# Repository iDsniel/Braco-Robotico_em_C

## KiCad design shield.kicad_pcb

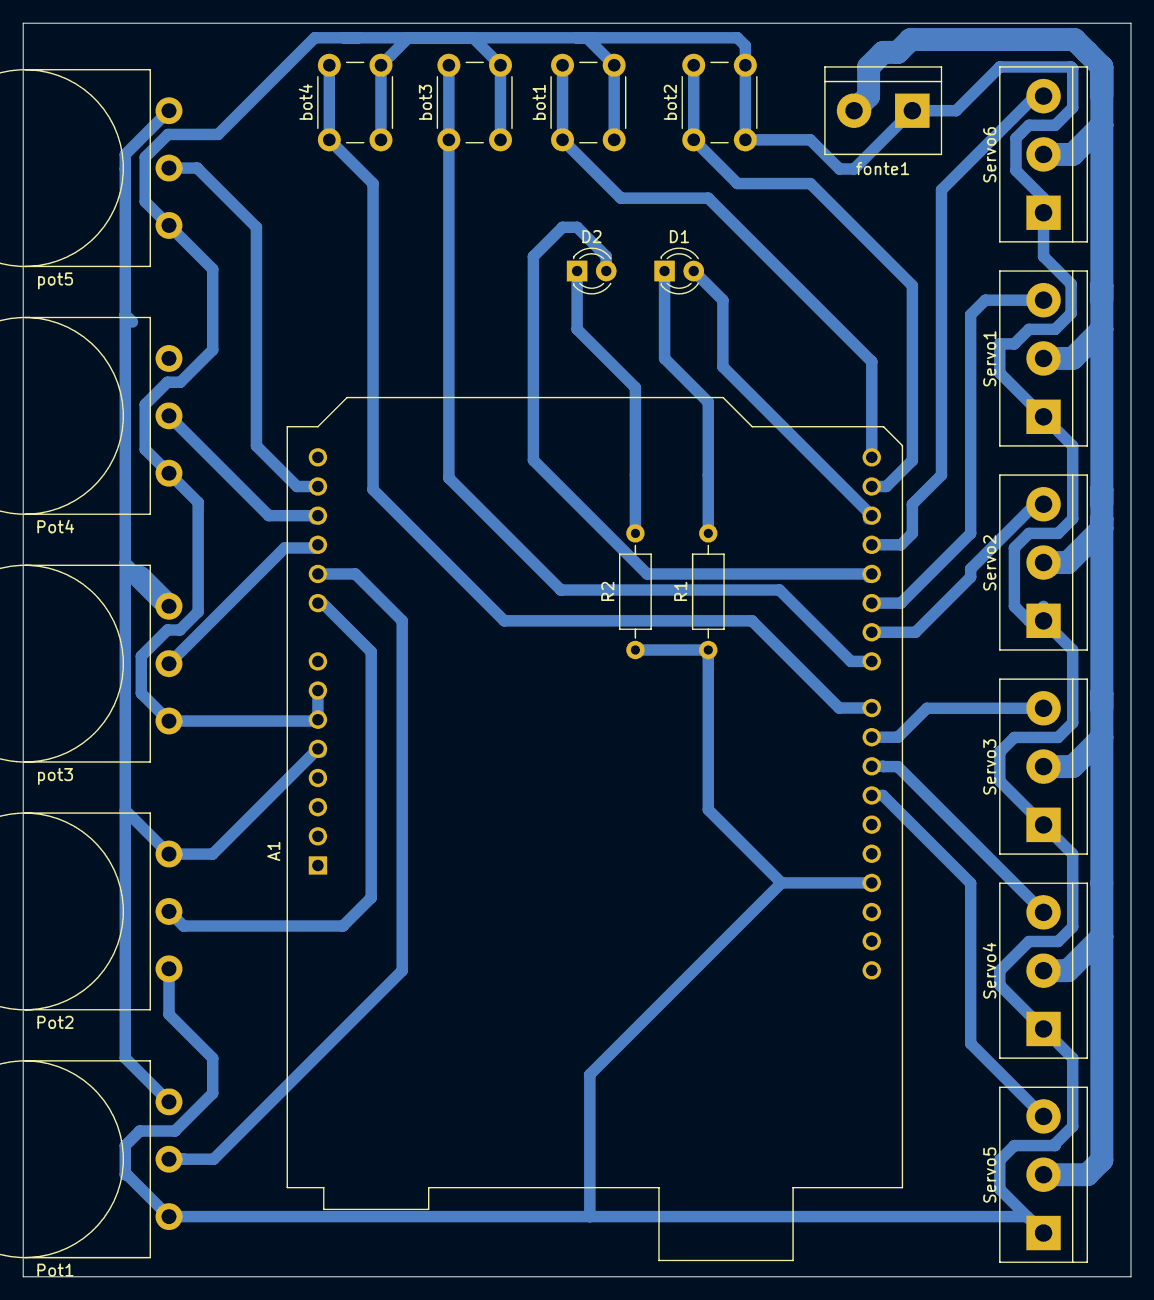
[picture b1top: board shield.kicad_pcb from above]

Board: 2 copper layers, 96.5 x 109.2 mm, 21 parts (0 on the bottom side), 22 nets.

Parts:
A1: Arduino_UNO_R3
D1, D2: LED; LED_D3.0mm
Pot1, Pot2, Pot4: Conn_01x03_Male; Potentiometer_Omeg_PC16BU_Vertical
R1, R2: R; R_Axial_DIN0207_L6.3mm_D2.5mm_P10.16mm_Horizontal
Servo1, Servo2, Servo3, Servo4, Servo5, Servo6: Conn_01x03_Male; TerminalBlock_bornier-3_P5.08mm
bot1, bot2, bot3, bot4: Conn_01x02_Male; SW_PUSH_6mm
fonte1: Conn_01x02_Male; TerminalBlock_bornier-2_P5.08mm
pot3, pot5: Conn_01x03_Male; Potentiometer_Omeg_PC16BU_Vertical

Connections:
/5V: A1.5, Pot1.1, Pot2.1, Pot4.1, pot3.1, pot5.1
/A0: A1.9, Pot2.2
/A1: A1.10, Pot1.2
/A2: A1.11, pot3.2
/A3: A1.12, Pot4.2
/A4: A1.13, pot5.2
/D0: A1.15, bot1.1
/D1: A1.16, bot2.1
/D2: A1.17, D1.2
/D3: A1.18, Servo6.3
/D4: A1.19, D2.2
/D5: A1.20, Servo1.3
/D6: A1.21, Servo2.3
/D7: A1.22, bot3.1
/D8: A1.23, bot4.1
/D9: A1.24, Servo3.3
/D10: A1.25, Servo4.3
/D11: A1.26, Servo5.3
/Vin: Servo1.2, Servo2.2, Servo3.2, Servo4.2, Servo5.2, Servo6.2, fonte1.2
GND: A1.6, A1.7, A1.29, Pot1.3, Pot2.3, Pot4.3, R1.1, R2.1, Servo1.1, Servo2.1, Servo3.1, Servo4.1, Servo5.1, Servo6.1, bot1.2, bot2.2, bot3.2, bot4.2, fonte1.1, pot3.3, pot5.3
unnamed: D1.1, R1.2
unnamed: D2.1, R2.2
